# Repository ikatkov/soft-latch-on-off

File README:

# Software latch on-off switch

source https://www.eevblog.com/forum/beginners/push-button-power-circuit-for-arduino-trying-to-modify-it-for-12v-input/

The button turns on the P-MOSFET when pushed, and also pulls the Arduino GPIO low so button pushes can be detected. The diodes keep the GPIO level and PMOS gate level separate.   

To keep the power on after the user releases the button, enable the GPIO's weak pullup, which keeps the N-MOSFET gate high, which keeps the P-MOSFET on.  N.B. The N-MOSFET gate pulldown *MUST* be large compared to the Arduino internal weak pullup, which is max. 50K.

To turn the power off, the Arduino sets the GPIO to Output Low.  Power off will be delayed if the user is holding the button down.  Holding the button down wont force poweroff if the Arduino is crashed.

# Fabrication

<a href="https://oshpark.com/shared_projects/e5mTrhY4"></img></a>

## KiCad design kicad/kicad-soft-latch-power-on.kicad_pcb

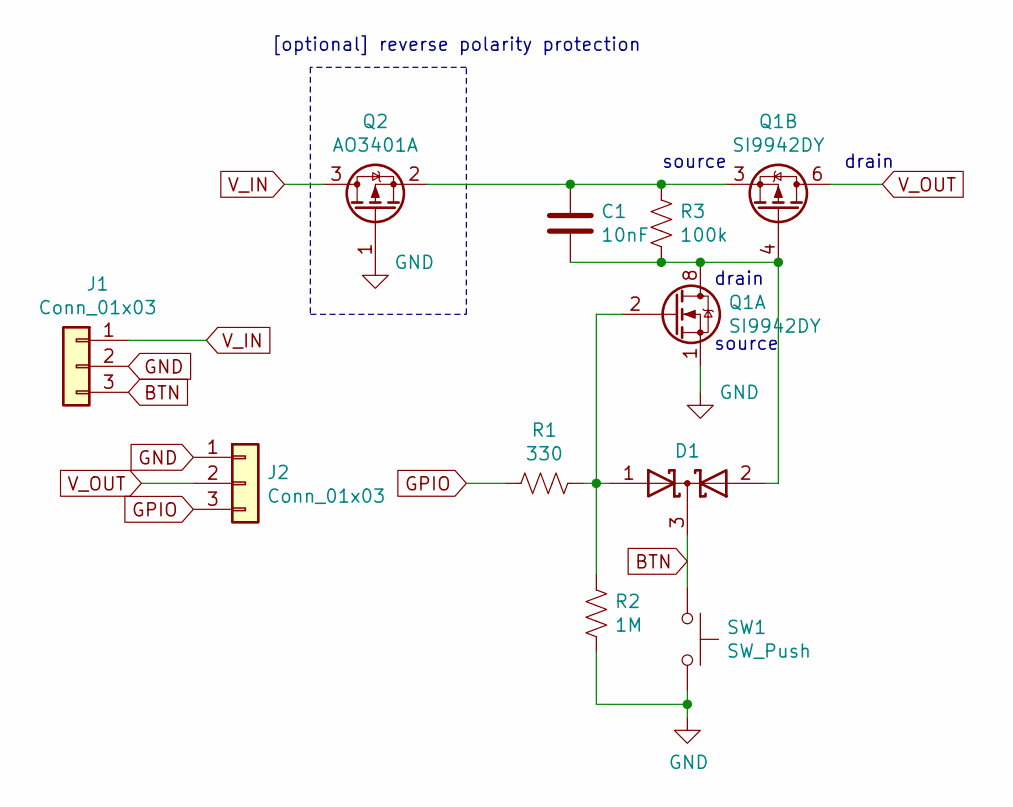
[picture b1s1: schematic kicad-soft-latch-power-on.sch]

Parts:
C1: 10nF; C_Disc_D4.7mm_W2.5mm_P5.00mm
D1: D_Schottky_x2_KCom_AAK; SOT-23
J1, J2: Conn_01x03; PinHeader_1x03_P2.54mm_Vertical
Q1: SI9942DY; SOIC-8_3.9x4.9mm_P1.27mm
Q2: AO3401A; SOT-23
R1: 330; R_Axial_DIN0204_L3.6mm_D1.6mm_P5.08mm_Horizontal
R2: 1M; R_Axial_DIN0204_L3.6mm_D1.6mm_P5.08mm_Horizontal
R3: 100k; R_Axial_DIN0204_L3.6mm_D1.6mm_P5.08mm_Horizontal
SW1: SW_Push; SW_PUSH_6mm

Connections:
BTN: D1.3 (K), J1.3, SW1.1
GND: J1.2, J2.1, Q1.1 (S), Q2.1 (G), R2.2, SW1.2
GPIO: J2.3, R1.2
unnamed: C1.1, Q1.3 (1), Q2.2 (S), R3.1
unnamed: C1.2, D1.2 (A), Q1.4 (G), Q1.7 (D), Q1.8 (D), R3.2
unnamed: D1.1 (A), Q1.2 (G), R1.1, R2.1
V_IN: J1.1, Q2.3 (D)
V_OUT: J2.2, Q1.5 (D), Q1.6 (D)

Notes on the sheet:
drain
source
[optional] reverse polarity protection

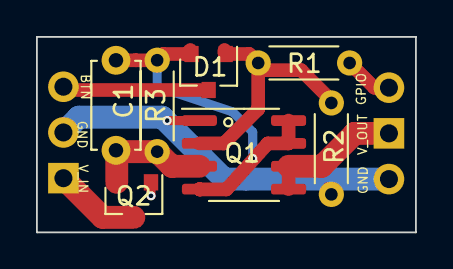
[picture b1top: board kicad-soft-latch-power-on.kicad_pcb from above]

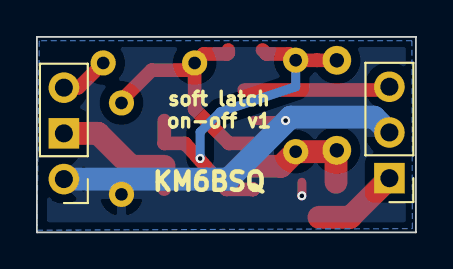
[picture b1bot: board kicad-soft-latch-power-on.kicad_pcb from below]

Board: 2 copper layers, 21.1 x 10.9 mm, 9 parts (2 on the bottom side), 8 nets.

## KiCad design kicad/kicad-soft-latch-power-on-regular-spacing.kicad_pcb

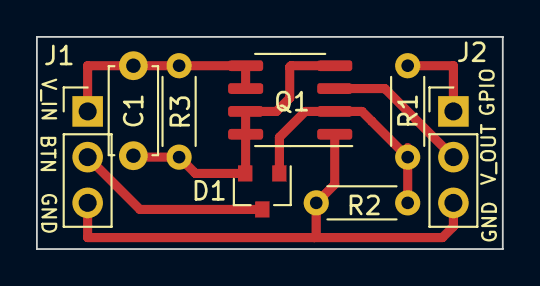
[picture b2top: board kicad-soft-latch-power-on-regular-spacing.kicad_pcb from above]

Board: 2 copper layers, 25.9 x 11.8 mm, 8 parts (0 on the bottom side), 7 nets.

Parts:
C1: 10nF; C_Disc_D4.7mm_W2.5mm_P5.00mm
D1: D_Schottky_x2_KCom_AAK; SOT-23
J1, J2: Conn_01x03; PinHeader_1x03_P2.54mm_Vertical
Q1: SI9942DY; SOIC-8_3.9x4.9mm_P1.27mm
R1: 330; R_Axial_DIN0204_L3.6mm_D1.6mm_P5.08mm_Horizontal
R2: 1M; R_Axial_DIN0204_L3.6mm_D1.6mm_P5.08mm_Horizontal
R3: 100k; R_Axial_DIN0204_L3.6mm_D1.6mm_P5.08mm_Horizontal

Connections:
BTN: D1.3, J1.2
GND: J1.3, J2.3, Q1.1, R2.2
GPIO: J2.1, R1.2
unnamed: C1.2, D1.2, Q1.4, Q1.7, Q1.8, R3.2
unnamed: D1.1, Q1.2, R1.1, R2.1
V_IN: C1.1, J1.1, Q1.5, Q1.6, R3.1
V_OUT: J2.2, Q1.3

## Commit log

2021-11-26 readme
2021-11-26 kicad sources
2021-11-26 logic update
2021-11-26 added render
2021-11-26 more images
2021-11-26 move files
2021-11-26 markdown
2021-11-26 renamed README
2021-11-26 updare schematic
2021-11-26 width fix
2021-11-28 pcb update
2021-12-03 add reverse polarity protection
2021-12-12 final version with TH parts
